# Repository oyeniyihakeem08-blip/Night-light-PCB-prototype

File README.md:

# Wireless Smart Night Light System

A smart, motion-sensing LED night light that runs straight from the mains, keeps working through power cuts on its own battery, and is controlled by a paired wireless remote.

I designed and built both custom PCBs end to end: schematic, PCB layout, power design, component selection and firmware for **both** the light and the remote.

## Highlights

- **Mains to light, all on one board:** 100 to 240 VAC input, isolated 5 V conversion, battery charging, 3.3 V logic, RF, sensing and a six-LED lighting array.
- **Seamless battery backup:** an 18650 Li-ion cell takes over automatically during a power outage, designed for about 24 hours of operation.
- **Smart behaviour:** the light turns on only when it is dark **and** someone moves, then stays on while motion continues.
- **Secure pairing:** a remote pairs with the light using a random 32-bit token, then talks to it on a private radio address that only that light listens to.
- **Hardware-level battery protection:** a nanopower comparator with hysteresis shuts the 3.3 V rail down at low battery, without depending on firmware.
- **Battery-friendly remote:** the remote sleeps between button presses and wakes on demand, so a small battery goes a long way.

## Hardware

### Main unit (the night light)

| Block | Part | Role |
| --- | --- | --- |
| Mains conversion | HLK-5M05 | Isolated 100 to 240 VAC to 5 V module, 5 W |
| Charger and power path | BQ24074RGT | Charges the battery, powers the system from the supply, switches to battery during an outage |
| Battery | 18650 Li-ion, 3000 mAh | Backup energy storage |
| Low-battery switching | TLV3012 comparator + AO3400A + AO3407A | Hardware cutoff with hysteresis |
| 3.3 V regulator | TLV75533 | Clean rail for MCU, RF and PIR |
| Microcontroller | STM32G031K8T6 | State machine, RF, sensing, LED control |
| Wireless | nRF24L01+ | 2.4 GHz link to the remote |
| Motion sensing | BISS0001 + PIR element | Presence detection |
| Light sensing | GL5528 LDR | Day/night detection via the ADC |
| Lighting | 6x Samsung LM281B+ (SPMWH1228MD5WATUVK) | Illumination, driven through an AO3400A MOSFET |
| Programming | SWD Tag-Connect | Flash and debug the STM32 |

### Wireless remote

| Block | Part | Role |
| --- | --- | --- |
| Microcontroller | ATtiny1616 | Remote controller |
| Wireless | nRF24L01+ | 2.4 GHz link to the light |
| Inputs | 3 buttons | Power, Sensor On, Sensor Off |
| Power | 2x AAA | Direct 3 V operation, no regulator needed |

### Board views

| | Design | Fabricated |
|---|---|---|
| **Front** |  |  |
| **Back** |  |  |

### Schematic

## Engineering decisions

### Charger, power path and input limiting

The BQ24074 is set for a **500 mA** charge current (1.8 k ISET resistor) and a **600 mA input current limit** (2.7 k ILIM resistor). The input limit is deliberate: it keeps total draw within what the HLK-5M05 can supply and prevents the module from overheating inside a compact enclosure.

### Low-battery cutoff in hardware, with hysteresis

A TLV3012 nanopower comparator with a built-in reference watches the battery through a 174 k / 100 k divider. A 1 M feedback resistor adds **hysteresis**, so the circuit turns the system **off at about 3.4 V** and only turns it **back on at about 3.6 V**. The comparator drives an N-MOSFET (AO3400A) that controls a high-side P-MOSFET (AO3407A) feeding the 3.3 V regulator. The result is a clean shutdown with no oscillation, and no dependence on firmware to protect the battery.

### Low-noise LED drive

Dedicated constant-current ICs (such as NSI45020 and AL5809) were evaluated and rejected: they need voltage headroom that is not available as the battery falls from 4.2 V towards 3.4 V. Instead, the six LEDs each have a 33 ohm series resistor and are switched through a MOSFET. It works across the full battery range, adds no switching noise and keeps the part count low.

### A 3.3 V rail chosen for the radio

The TLV75533 was picked for its fast transient response, which handles the current spikes of the nRF24L01+, and for its low output noise, which keeps the PIR and RF stable.

### Isolation from the mains

Mains conversion is handled by a pre-built isolated AC-DC module, so everything downstream is low voltage. It also keeps the design simpler and lowers certification risk compared with a discrete flyback.

### Battery connector protection

A P-MOSFET (AO3407A) sits in series with the battery connector, which provides reverse-polarity protection.

### Light sensor is read only while the light is off

If the LDR were read while the LEDs are on, the light would be measuring its own output and the system would flip-flop between states. The firmware therefore reads the LDR only when the light is off, and waits for it to settle after the light switches off before sampling.

## Design evolution

I started this project with a written system architecture, and the final board differs from it in three places. I made each change deliberately during development.

| Area | Initial architecture | Final design | Why it changed |
| --- | --- | --- | --- |
| PIR front-end | NCS36000 | BISS0001 | The original chip could not be sourced, so I found a suitable replacement and redesigned the sensor circuit around it to keep the build moving without compromising the design. |
| Remote buttons | 2 buttons | 3 buttons (Power, Sensor On, Sensor Off) | Improved during development. Separate Sensor On and Sensor Off buttons make the remote clearer and more direct to use, while Power handles toggling, pairing and reset. |
| Pairing | Remote sends a unique ID, which the light stores | Random 32-bit token, stored with the remote's ID, then a private radio address | Chosen for security and for a better experience for users and engineers (see below). |

### Why pairing was redesigned

The first plan relied on a fixed unique ID from the remote. That works, but it leaves a reusable identifier that never changes, and it keeps all traffic on one shared address where neighbouring units can interfere with each other.

The final scheme is more robust:

- **A fresh secret for every pairing.** The light generates a 32-bit token each time a remote is paired, so there is no fixed identifier to copy or reuse. Every command afterwards must carry that token, and the light ignores anything that does not match.
- **A private address after pairing.** Once paired, commands travel on a private radio address that belongs to that remote and that only its light listens to. The shared public address is used only for pairing and factory reset, which keeps everyday traffic off it and reduces interference between nearby units.
- **A short, clear pairing window.** Pairing is only open for 60 seconds after power-up, with LED feedback at every step, so users and installers always know what state the light is in.
- **A safe way out.** A 6 second factory reset clears the stored pairing, so a lost or replaced remote never leaves the light locked to a remote nobody has.

## How it behaves

### Light modes

| Mode | What the light does |
| --- | --- |
| Smart Idle | Light is off. The LDR is read to check if the room is dark. If it is dark and the PIR sees motion, the light turns on and moves to Smart Active. If the room is bright, motion is ignored. |
| Smart Active | Light is on. The LDR is no longer read, so room lights or sunrise do not switch it off. Every movement restarts a 60 second countdown, and when 60 seconds pass with no motion the light turns off and returns to Smart Idle. |
| Forced On | Power pressed while sensors are enabled. The light turns on and stays on. Motion and the LDR are ignored and the 60 second timer is paused. |
| Manual Mode | Sensor Off pressed. Both sensors are disabled and the light is a plain remote-controlled lamp: Power turns it on, Power again turns it off. |

### Remote buttons

| Button | Action |
| --- | --- |
| Power | Tap: toggle the light. Hold 3 seconds: start pairing. Hold 6 seconds: factory reset. |
| Sensor On | Tap: re-enable the motion and light sensors. |
| Sensor Off | Tap: disable the sensors and switch to manual mode. |

### Pairing, step by step

1. On first power-up the light enters pairing mode for up to 60 seconds. Its LED blinks slowly (1 second on, 2 seconds off) while it listens on the public address.
2. On the remote I hold Power for 3 seconds. The remote sends a pairing request and blinks its LED (1 second on, 2 seconds off) while it waits.
3. The light generates a random 32-bit token, stores it with the remote's address in permanent memory and replies with a confirmation.
4. The remote receives the confirmation, blinks twice quickly and switches to its private address. The light confirms with a long double blink (3 seconds on, 2 off, 3 on), and normal operation starts.
5. If nobody pairs within 60 seconds, the light stops blinking and runs in smart (sensor) mode. Until a remote is paired, it cannot be switched on or off or have its sensor mode changed.

To pair a new remote later, for example after losing the first, I hold Power for 6 seconds. This sends a factory reset, which clears the stored pairing; the light blinks 6 times and goes back into pairing mode. Factory reset is the only command the light accepts on the public address after pairing.

### LED feedback

The light's LED only blinks to report:

- Slow blink (1 second on, 2 seconds off): pairing mode, waiting for a remote.
- Long double blink (3 seconds on, 2 off, 3 on): paired successfully.
- One short flash: sensors turned on.
- Two short flashes: sensors turned off.

The remote LED responds to every button press: one blink means the light received the command, three fast blinks mean it failed.

### Remote power saving

The remote does not run a loop. It sleeps fully between presses, drawing under a microamp, and wakes in microseconds when any button is pressed. It then sends its command, waits for the acknowledgement, blinks its LED and goes straight back to sleep, so two AAA cells go a long way.

## Firmware and radio link

Both units run PlatformIO projects using the Arduino framework with the RF24 library for the nRF24L01+. The firmware is layered so that hardware drivers, the radio, pairing and the application logic are kept in separate modules.

### Radio settings

| Setting | Value |
| --- | --- |
| Frequency channel | 76 (2.476 GHz) |
| Data rate | 250 kbps |
| Transmit power | PA_LOW |
| Auto-retry | up to 15 retries (delay setting 5) |
| Public address (pipe 0) | `E7:E7:E7:E7:E7`, used only for pairing and factory reset |
| Private address (pipe 1) | the remote's own unique 5-byte address, assigned at pairing |

250 kbps gives the best receiver sensitivity and range on the nRF24L01+, and low transmit power keeps current draw down on the remote's two AAA cells.

### Packet format

Every message is a fixed 11 byte packet:

```c
struct Packet {
    uint8_t  cmd;            // command code
    uint32_t token;          // pairing token
    uint8_t  remote_addr[5]; // remote's private address
    uint8_t  nonce;          // per-message value
};
```

| Command | Code | Sent on |
| --- | --- | --- |
| CMD_PAIR | 0x01 | public address |
| CMD_PAIR_ACK | 0x02 | public address |
| CMD_FACTORY_RESET | 0x03 | public address |
| CMD_POWER_ON | 0x10 | private address |
| CMD_POWER_OFF | 0x11 | private address |
| CMD_SENSOR_ON | 0x12 | private address |
| CMD_SENSOR_OFF | 0x13 | private address |

### How the light handles a packet

- On the public address (pipe 0), a paired light accepts only a factory reset.
- On the private address (pipe 1), the light checks the token first. A packet with a wrong token is dropped; a valid one goes to the light controller, which acts on the command.
- The pairing token is built from the lowest bit of 32 LDR ADC readings, mixed with the system timer, so it does not depend on a fixed seed. It is stored in EEPROM so pairing survives power cuts and battery loss.
- The bulb runs the independent watchdog (IWDG) so that a stuck firmware loop resets itself.

## Manufacturing

BOM, Gerber and pick-and-place files for JLCPCB / LCSC.

## Repository layout

```text
.
├── README.md
├── Night light PCB.kicad_pro      # KiCad project
├── Night light PCB.kicad_sch      # schematic
├── Night light PCB.kicad_pcb      # PCB layout
├── fp-lib-table                   # footprint library paths
├── sym-lib-table                  # symbol library paths
├── Footprint/                     # custom footprint libraries
├── Symbol/                        # custom symbol libraries
├── 3D Model/                      # 3D models used by the footprints
├── Night light PCB (Kicad and production files)/
│   └── Design filess/
│       ├── Night light PCB 3D model/
│       │   ├── Night Light board.step
│       │   ├── Night Light remote board.step
│       │   └── Night light PCB.step
│       ├── production/            # JLCPCB manufacturing outputs
│       │   ├── backups/
│       │   ├── bom.csv
│       │   ├── designators.csv
│       │   ├── netlist.ipc
│       │   ├── Night_light_PCB.zip
│       │   └── positions.csv
│       ├── Night light PCB BOM .csv
│       ├── Night light PCB-F_Fab.svg
│       ├── Night light PCB-NPTH-drl_map.pdf
│       ├── Night light PCB-PTH-drl_map.pdf
│       └── Night light Schematics.pdf
├── Firmware source file/          # firmware source projects
├── firmwares/                     # firmware builds
├── Documents/                     # project documents
└── Images/                        # photos, layouts and schematic used in this README
```

## Author

Hakeem Oyebisi · [oyebisihakeem@gmail.com](mailto:oyebisihakeem@gmail.com) · [GitHub](https://github.com/oyeniyihakeem08-blip)

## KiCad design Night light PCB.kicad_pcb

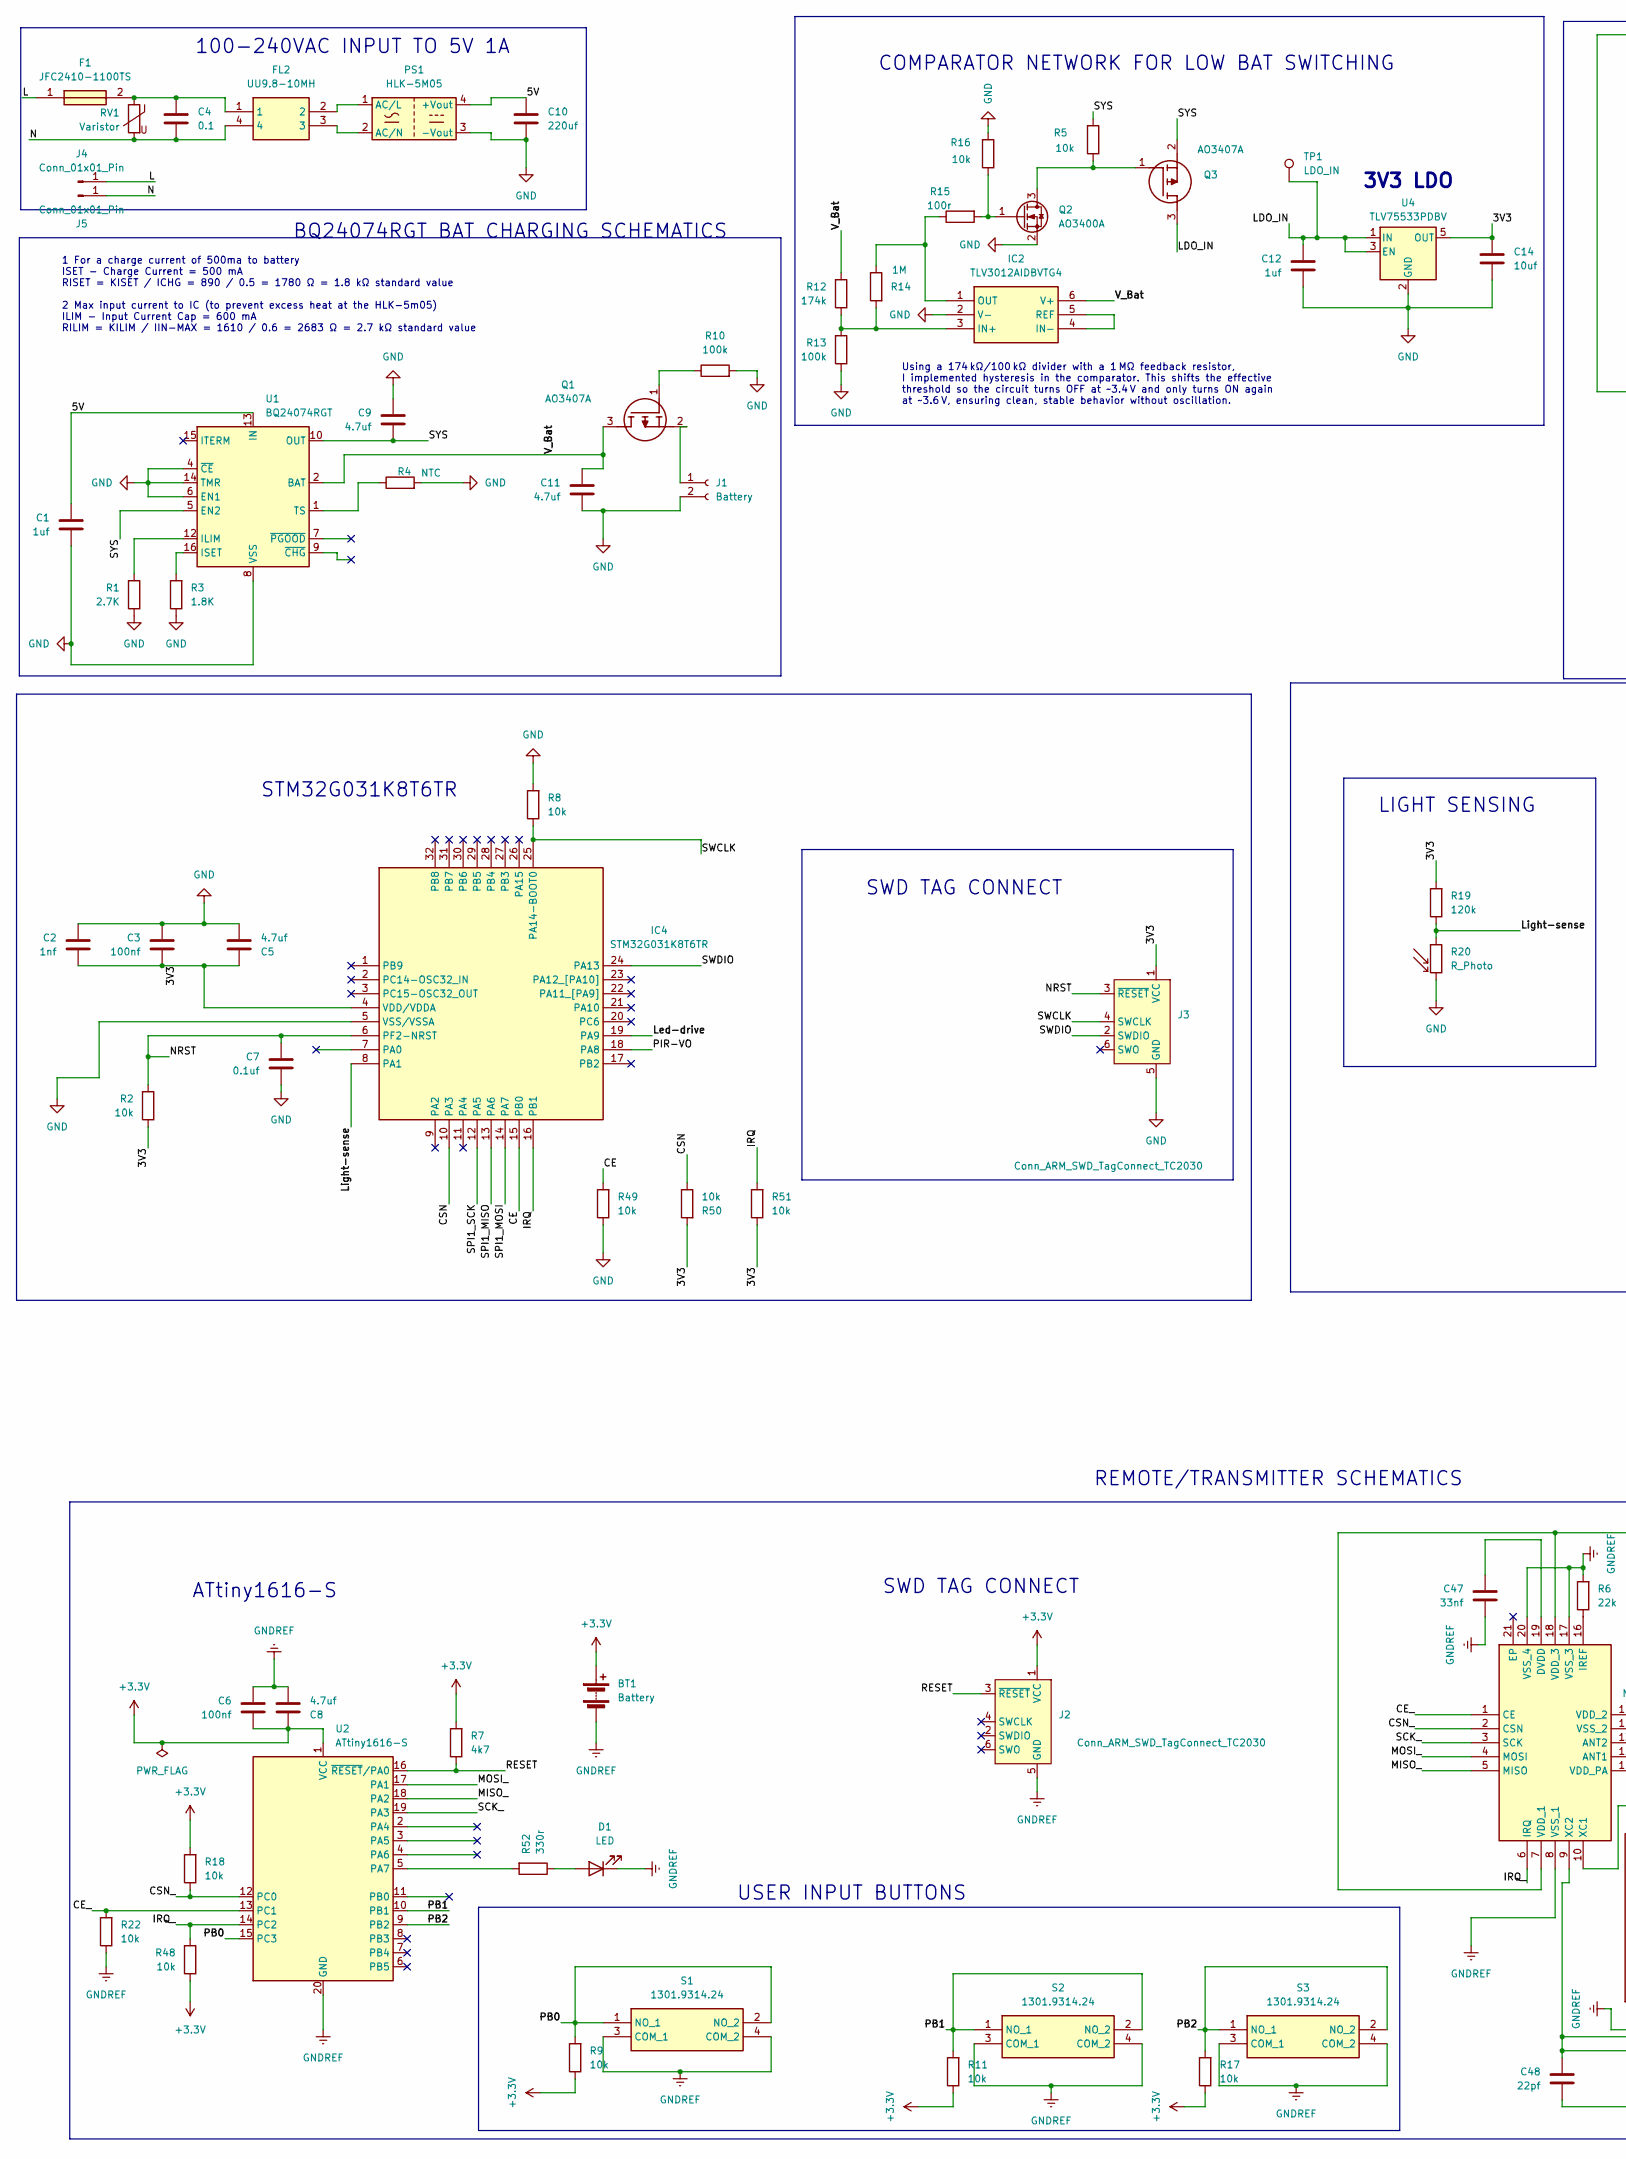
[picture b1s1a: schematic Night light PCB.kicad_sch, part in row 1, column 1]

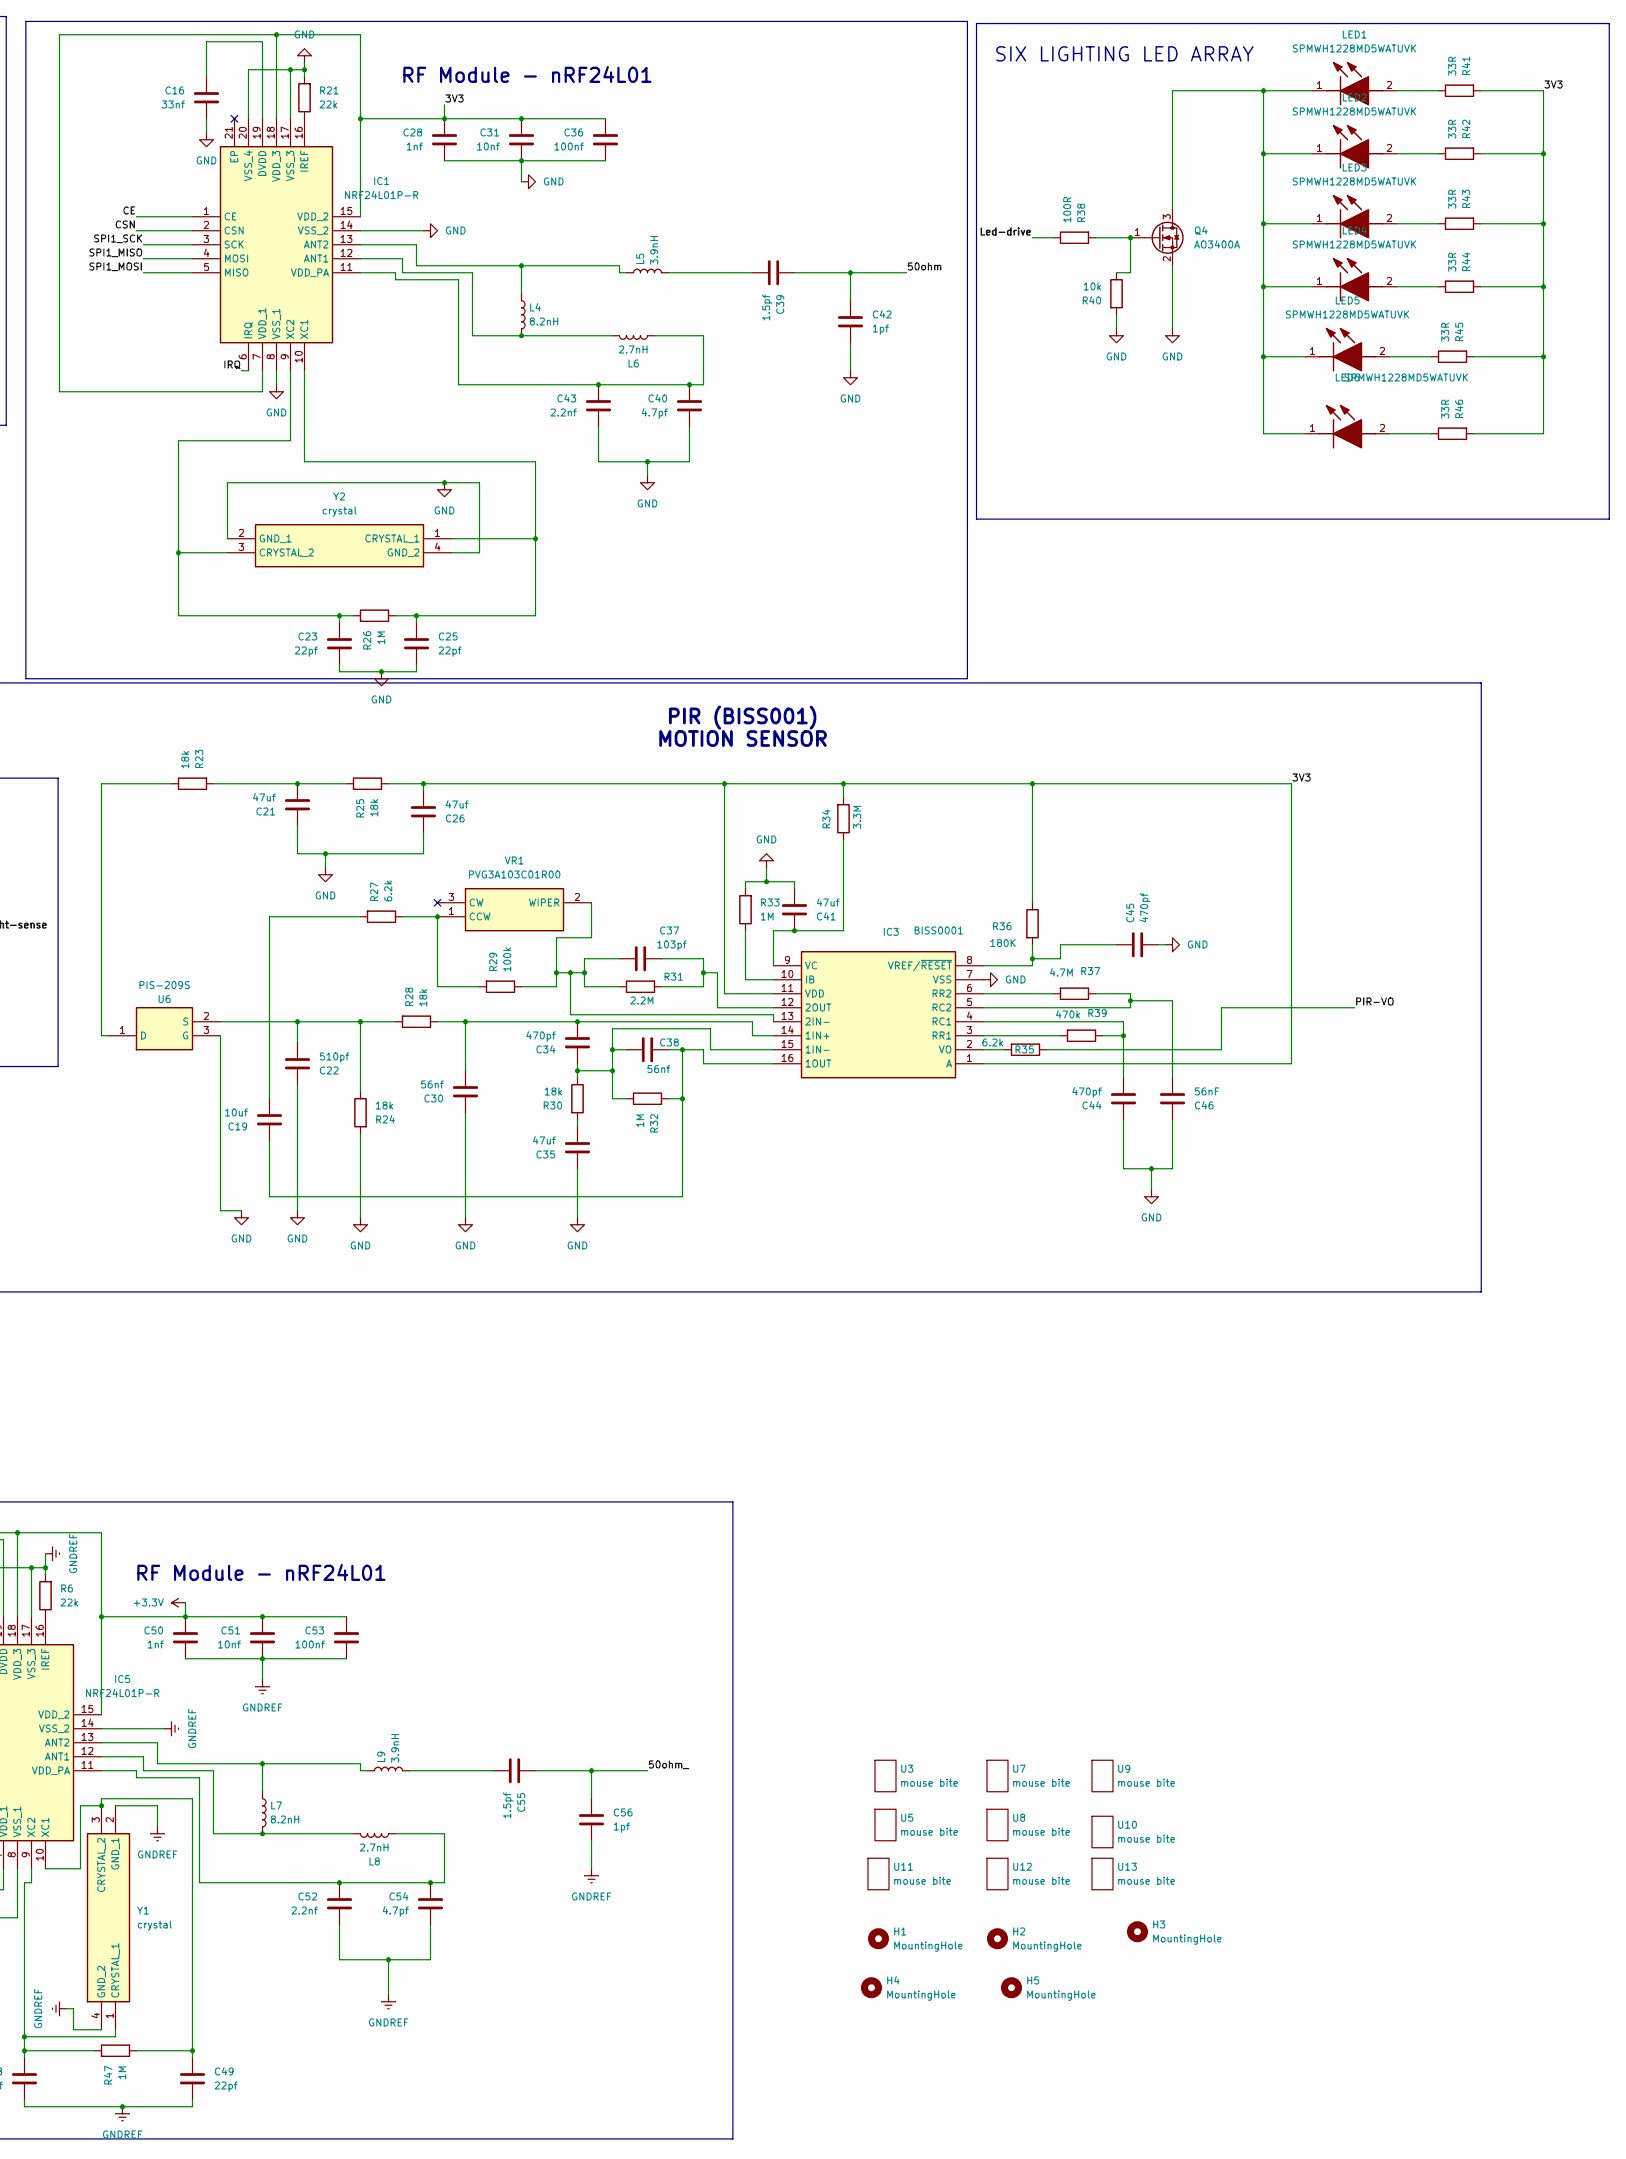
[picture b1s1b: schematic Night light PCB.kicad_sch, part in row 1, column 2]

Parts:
BT1: Battery; BatteryHolder_Keystone_2468_2xAAA; LCSC Part # BC2AAAPC
C1: 1uf; C_0402_1005Metric; LCSC Part # C29266
C2: 1nf; C_0805_2012Metric; LCSC Part # C94121
C3, C6: 100nf; C_0805_2012Metric; LCSC Part # C49678
C4: 0.1; C_Rect_L13.0mm_W8.0mm_P10.00mm_FKS3_FKP3_MKS4; LCSC Part # C46638858
C5, C8, C9, C11: 4.7uf; C_0805_2012Metric; LCSC Part # C98192
C7: 0.1uf; C_0805_2012Metric; LCSC Part # C49678
C10: 220uf; C_Elec_6.3x7.7; LCSC Part # C2887273
C12: 1uf; C_0805_2012Metric; LCSC Part # C28323
C14: 10uf; C_0805_2012Metric; LCSC Part # C95841
C16, C47: 33nf; C_0402_1005Metric; LCSC Part # C106862
C19: 10uf; C_1210_3225Metric; LCSC Part # C2918502
C21, C26, C35, C41: 47uf; C_1210_3225Metric; LCSC Part # C5440143
C22: 510pf; C_0402_1005Metric; LCSC Part # C18185763
C23, C25, C48, C49: 22pf; C_0402_1005Metric; LCSC Part # C277482
C28, C50: 1nf; C_0402_1005Metric; LCSC Part # C76947
C30, C38: 56nf; C_0402_1005Metric; LCSC Part # C36911349
C31, C51: 10nf; C_0402_1005Metric; LCSC Part # C15195
C34, C44, C45: 470pf; C_0402_1005Metric; LCSC Part # C701296
C36, C53: 100nf; C_0402_1005Metric; LCSC Part # C60474
C37: 103pf; C_0402_1005Metric; LCSC Part # C327009
C39, C55: 1.5pf; C_0402_1005Metric; LCSC Part # C1552
C40, C54: 4.7pf; C_0402_1005Metric; LCSC Part # C1569
C42, C56: 1pf; C_0402_1005Metric; LCSC Part # C710646
C43, C52: 2.2nf; C_0402_1005Metric; LCSC Part # C2987940
C46: 56nF; C_0402_1005Metric; LCSC Part # C36911349
D1: LED; LED_0402_1005Metric; LCSC Part # C21260817
F1: JFC2410-1100TS; FUSC10131X330N; Manufacturer_Part_Number SF-3812TL100T-2; Mouser Part Number 652-SF-3812TL100T-2
FL2: UU9.8-10MH; UU9810MH; Manufacturer_Part_Number UU9.8-10MH; LCSC Part # C148474
H1, H2, H3, H4, H5: MountingHole; MountingHole_3.2mm_M3
IC1, IC5: NRF24L01P-R; QFN50P400X400X95-21N-D; Manufacturer_Part_Number NRF24L01P-R; Mouser Part Number 949-NRF24L01P-R
IC2: TLV3012AIDBVTG4; SOT95P280X145-6N; Manufacturer_Part_Number TLV3012AIDBVTG4; Mouser Part Number 595-TLV3012AIDBVTG4
IC3: BISS0001; SOIC127P600X160-16N; Manufacturer_Part_Number BISS0001; LCSC Part # C18164474
IC4: STM32G031K8T6TR; QFP80P900X900X160-32N; Manufacturer_Part_Number STM32G031K8T6TR; Mouser Part Number 511-STM32G031K8T6TR
J1: Battery; JST_EH_B2B-EH-A_1x02_P2.50mm_Vertical; LCSC Part # C160262
J2, J3: Conn_ARM_SWD_TagConnect_TC2030; Tag-Connect_TC2030-IDC-FP_2x03_P1.27mm_Vertical
J4, J5: Conn_01x01_Pin; TestPoint_Keystone_5010-5014_Multipurpose
L4, L7: 8.2nH; L_0402_1005Metric; LCSC Part # C84404
L5, L9: 3.9nH; L_0402_1005Metric; LCSC Part # C5452416
L6, L8: 2.7nH; L_0402_1005Metric; LCSC Part # C77108
LED1, LED2, LED3, LED4, LED5, LED6: SPMWH1228MD5WATUVK; Manufacturer_Part_Number SPMWH1228MD5WATUVK; LCSC Part # 1510-SPMWH1228MD7WATUVKTR-ND
PS1: HLK-5M05; Converter_ACDC_Hi-Link_HLK-5Mxx; LCSC Part # C209907
Q1, Q3: AO3407A; SOT95P280X125-3N; Manufacturer_Part_Number AO3407A; LCSC Part # C15155
Q2, Q4: AO3400A; SOT-23; LCSC Part # C20917
R1: 2.7K; R_0402_1005Metric; LCSC Part # C138017
R2, R5, R8, R9, R11, R16, R17, R18, R22, R40, R48, R49, R50, R51: 10k; R_0402_1005Metric; LCSC Part # C60490
R3: 1.8K; R_0402_1005Metric; LCSC Part # C163481
R4: NTC; R_0402_1005Metric
R6, R21: 22k; R_0402_1005Metric; LCSC Part # C82868
R7: 4k7; R_0402_1005Metric; LCSC Part # C105871
R10, R13, R29: 100k; R_0402_1005Metric; LCSC Part # C60491
R12: 174k; R_0402_1005Metric; LCSC Part # C4214842
R14, R26, R32, R33, R47: 1M; R_0402_1005Metric; LCSC Part # C138033
R15: 100r; R_0402_1005Metric; LCSC Part # C106232
R19: 120k; R_0402_1005Metric; LCSC Part # C60490
R20: R_Photo; R_LDR_5.0x4.1mm_P3mm_Vertical; LCSC Part # C125627
R23, R24, R25, R28, R30: 18k; R_0402_1005Metric; LCSC Part # C138044
R27, R35: 6.2k; R_0402_1005Metric; LCSC Part # C137946
R31: 2.2M; R_0402_1005Metric; LCSC Part # C203143
R34: 3.3M; R_0402_1005Metric; LCSC Part # C482174
R36: 180K; R_0402_1005Metric; LCSC Part # C25760
R37: 4.7M; R_0402_1005Metric; LCSC Part # C3013173
R38: 100R; R_0402_1005Metric; LCSC Part # C106232
R39: 470k; R_0402_1005Metric; LCSC Part # C137976
R41, R42, R43, R44, R45, R46: 33R; R_0805_2012Metric; LCSC Part # C2907220
R52: 330r; R_0402_1005Metric; LCSC Part # C2097621
RV1: Varistor; RV_Disc_D12mm_W4.5mm_P7.5mm; LCSC Part # C2839517
S1, S2, S3: 1301.9314.24; 1301931424; Manufacturer_Part_Number 1301.9314.24; Mouser Part Number 693-1301.9314.24
TP1: LDO_IN; TestPoint_Pad_D4.0mm
U1: BQ24074RGT; VQFN-16-1EP_3x3mm_P0.5mm_EP1.6x1.6mm; LCSC Part # C54313
U2: ATtiny1616-S; SOIC-20W_7.5x12.8mm_P1.27mm; LCSC Part # C614136
U3, U5, U7, U8, U9, U10, U11, U12, U13: mouse bite; mouse-bite-2mm-4mm
U4: TLV75533PDBV; SOT-23-5; LCSC Part # C404027
U6: PIS-209S; PIS209S; Manufacturer_Part_Number PIS-209S
VR1: PVG3A103C01R00; Manufacturer_Part_Number PVG3A103C01R00; Mouser Part Number 81-PVG3A103C01R00
Y1, Y2: crystal; X322516MOB4SI; Manufacturer_Part_Number X322516MOB4SI; LCSC Part # C12668

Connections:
+3.3V: BT1.1 (+), C6.2, C8.1, C50.1, C51.1, C53.1, IC5.7 (VDD_1), IC5.15 (VDD_2), IC5.18 (VDD_3), J2.1 (VCC), R7.2, R9.1, R11.1, R17.1, R18.2, R48.1, U2.1 (VCC)
/3V3: C2.2, C3.2, C5.1, C14.1, C26.2, C28.1, C31.1, C36.1, IC1.7 (VDD_1), IC1.15 (VDD_2), IC1.18 (VDD_3), IC3.1 (A), IC3.11 (VDD), IC4.4 (VDD/VDDA), J3.1 (VCC), R2.1, R19.2, R25.1, R34.2, R36.1, R41.2, R42.2, R43.2, R44.2, R45.2, R46.2, R50.2, R51.1, U4.5 (OUT)
/5V: C1.1, C10.1, PS1.4 (+Vout), U1.13 (IN)
/50ohm: C39.1, C42.1
/50ohm_: C55.1, C56.1
/CE: IC1.1 (CE), IC4.15 (PB0), R49.2
/CE_: IC5.1 (CE), R22.2, U2.13 (PC1)
/CSN: IC1.2 (CSN), IC4.10 (PA3), R50.1
/CSN_: IC5.2 (CSN), R18.1, U2.12 (PC0)
/IRQ: IC1.6 (IRQ), IC4.16 (PB1), R51.2
/IRQ_: IC5.6 (IRQ), R48.2, U2.14 (PC2)
/L: F1.1, J4.1
/LDO_IN: C12.1, Q3.3 (D), TP1.1, U4.1 (IN), U4.3 (EN)
/Led-drive: IC4.19 (PA9), R38.1
/Light-sense: IC4.8 (PA1), R19.1, R20.1
/MISO_: IC5.5 (MISO), U2.18 (PA2)
/MOSI_: IC5.4 (MOSI), U2.17 (PA1)
/N: C4.2, FL2.4, J5.1, RV1.2
/NRST: C7.1, IC4.6 (PF2-NRST), J3.3 (~RESET), R2.2
/PB0: R9.2, S1.1 (NO_1), S1.2 (NO_2), U2.15 (PC3)
/PB1: R11.2, S2.1 (NO_1), S2.2 (NO_2), U2.10 (PB1)
/PB2: R17.2, S3.1 (NO_1), S3.2 (NO_2), U2.9 (PB2)
/PIR-VO: IC4.18 (PA8), R35.1
/RESET: J2.3 (~RESET), R7.1, U2.16 (~RESET/PA0)
/SCK_: IC5.3 (SCK), U2.19 (PA3)
/SPI1_MISO: IC1.4 (MOSI), IC4.13 (PA6)
/SPI1_MOSI: IC1.5 (MISO), IC4.14 (PA7)
/SPI1_SCK: IC1.3 (SCK), IC4.12 (PA5)
/SWCLK: IC4.25 (PA14-BOOT0), J3.4 (SWCLK), R8.1
/SWDIO: IC4.24 (PA13), J3.2 (SWDIO)
/SYS: C9.2, Q3.2 (S), R5.2, U1.5 (EN2), U1.10 (OUT), U1.11 (OUT)
/V_Bat: C11.1, IC2.6 (V+), Q1.3 (D), R12.2, U1.2 (BAT), U1.3 (BAT)
GND: C1.2, C2.1, C3.1, C5.2, C7.2, C9.1, C10.2, C11.2, C12.2, C14.2, C16.2, C21.1, C22.1, C23.2, C25.2, C26.1, C28.2, C30.1, C31.2, C35.1, C36.2, C40.2, C41.2, C42.2, C43.2, C44.1, C45.2, C46.1, IC1.8 (VSS_1), IC1.14 (VSS_2), IC1.17 (VSS_3), IC1.20 (VSS_4), IC2.2 (V-), IC3.7 (VSS), IC4.5 (VSS/VSSA), J1.2, J3.5 (GND), PS1.3 (-Vout), Q2.2 (S), Q4.2 (S), R1.1, R3.1, R4.2, R8.2, R10.2, R13.1, R16.2, R20.2, R21.2, R24.2, R33.2, R40.2, R49.1, U1.4 (~CE), U1.6 (EN1), U1.8 (VSS), U1.14 (TMR), U1.17 (VSS), U4.2 (GND), U6.3 (G), Y2.2 (GND_1), Y2.4 (GND_2)
GNDREF: BT1.2 (-), C6.1, C8.2, C47.2, C48.2, C49.2, C50.2, C51.2, C52.2, C53.2, C54.2, C56.2, D1.1 (K), IC5.8 (VSS_1), IC5.14 (VSS_2), IC5.17 (VSS_3), IC5.20 (VSS_4), J2.5 (GND), R6.2, R22.1, S1.3 (COM_1), S1.4 (COM_2), S2.3 (COM_1), S2.4 (COM_2), S3.3 (COM_1), S3.4 (COM_2), U2.20 (GND), Y1.2 (GND_1), Y1.4 (GND_2)
unnamed: C4.1, F1.2, FL2.1, RV1.1
unnamed: C19.2, R27.2
unnamed: C21.2, R23.2, R25.2
unnamed: C35.2, R30.2
unnamed: C39.2, L5.2
unnamed: C55.2, L9.2
unnamed: D1.2 (A), R52.1
unnamed: IC1.12 (ANT1), L4.2, L6.1
unnamed: IC1.13 (ANT2), L4.1, L5.1
unnamed: C16.1, IC1.19 (DVDD)
unnamed: IC1.16 (IREF), R21.1
unnamed: C40.1, C43.1, IC1.11 (VDD_PA), L6.2
unnamed: C25.1, IC1.10 (XC1), R26.1, Y2.1 (CRYSTAL_1)
unnamed: C23.1, IC1.9 (XC2), R26.2, Y2.3 (CRYSTAL_2)
unnamed: IC2.3 (IN+), R12.1, R13.2, R14.2
unnamed: IC2.4 (IN-), IC2.5 (REF)
unnamed: IC2.1 (OUT), R14.1, R15.1
unnamed: C30.2, C34.2, IC3.14 (1IN+), R28.1
unnamed: C34.1, C38.2, IC3.15 (1IN-), R30.1, R32.1
unnamed: C19.1, C38.1, IC3.16 (1OUT), R32.2
unnamed: C37.2, IC3.13 (2IN-), R29.1, R31.1, VR1.2 (WIPER)
unnamed: C37.1, IC3.12 (2OUT), R31.2
unnamed: IC3.10 (IB), R33.1
unnamed: C44.2, IC3.4 (RC1), R39.1
unnamed: C46.2, IC3.5 (RC2), R37.1
unnamed: IC3.3 (RR1), R39.2
unnamed: IC3.6 (RR2), R37.2
unnamed: C41.1, IC3.9 (VC), R34.1
unnamed: IC3.2 (VO), R35.2
unnamed: C45.1, IC3.8 (VREF/~RESET), R36.2
unnamed: IC5.12 (ANT1), L7.2, L8.1
unnamed: IC5.13 (ANT2), L7.1, L9.1
unnamed: C47.1, IC5.19 (DVDD)
unnamed: IC5.16 (IREF), R6.1
unnamed: C52.1, C54.1, IC5.11 (VDD_PA), L8.2
unnamed: C49.1, IC5.10 (XC1), R47.1, Y1.3 (CRYSTAL_2)
unnamed: C48.1, IC5.9 (XC2), R47.2, Y1.1 (CRYSTAL_1)
unnamed: J1.1, Q1.2 (S)
unnamed: LED1.2 (A), R41.1
unnamed: LED1.1 (K), LED2.1 (K), LED3.1 (K), LED4.1 (K), LED5.1 (K), LED6.1 (K), Q4.3 (D)
unnamed: LED2.2 (A), R42.1
unnamed: LED3.2 (A), R43.1
unnamed: LED4.2 (A), R44.1
unnamed: LED5.2 (A), R45.1
unnamed: LED6.2 (A), R46.1
unnamed: FL2.2, PS1.1 (AC/L)
unnamed: FL2.3, PS1.2 (AC/N)
unnamed: Q1.1 (G), R10.1
unnamed: Q2.3 (D), Q3.1 (G), R5.1
unnamed: Q2.1 (G), R15.2, R16.1
unnamed: Q4.1 (G), R38.2, R40.1
unnamed: R1.2, U1.12 (ILIM)
unnamed: R3.2, U1.16 (ISET)
unnamed: R4.1, U1.1 (TS)
unnamed: R52.2, U2.5 (PA7)
unnamed: R23.1, U6.1 (D)
unnamed: C22.2, R24.1, R28.2, U6.2 (S)
unnamed: R27.1, R29.2, VR1.1 (CCW)

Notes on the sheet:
REMOTE/TRANSMITTER SCHEMATICS
PIR (BISS001) MOTION SENSOR
3V3 LDO
SWD TAG CONNECT
BQ24074RGT BAT CHARGING SCHEMATICS
STM32G031K8T6TR
RF Module - nRF24L01
USER INPUT BUTTONS
1 For a charge current of 500ma to battery ISET - Charge Current = 500 mA RISET = KISET / ICHG = 890 / 0.5 = 1780 Ω = 1.8 kΩ standard value 2 Max input current to IC (to prevent excess heat at the HLK-5m05) ILIM - Input Current Cap = 600 mA RILIM = KILIM / IIN-MAX = 1610 / 0.6 = 2683 Ω = 2.7 kΩ sta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
COMPARATOR NETWORK FOR LOW BAT SWITCHING
SIX LIGHTING LED ARRAY
LIGHT SENSING
ATtiny1616-S
Using a 174 kΩ/100 kΩ divider with a 1 MΩ feedback resistor, I implemented hysteresis in the comparator. This shifts the effective threshold so the circuit turns OFF at ~3.4 V and only turns ON again at ~3.6 V, ensuring clean, stable behavior without oscillation.
100-240VAC INPUT TO 5V 1A

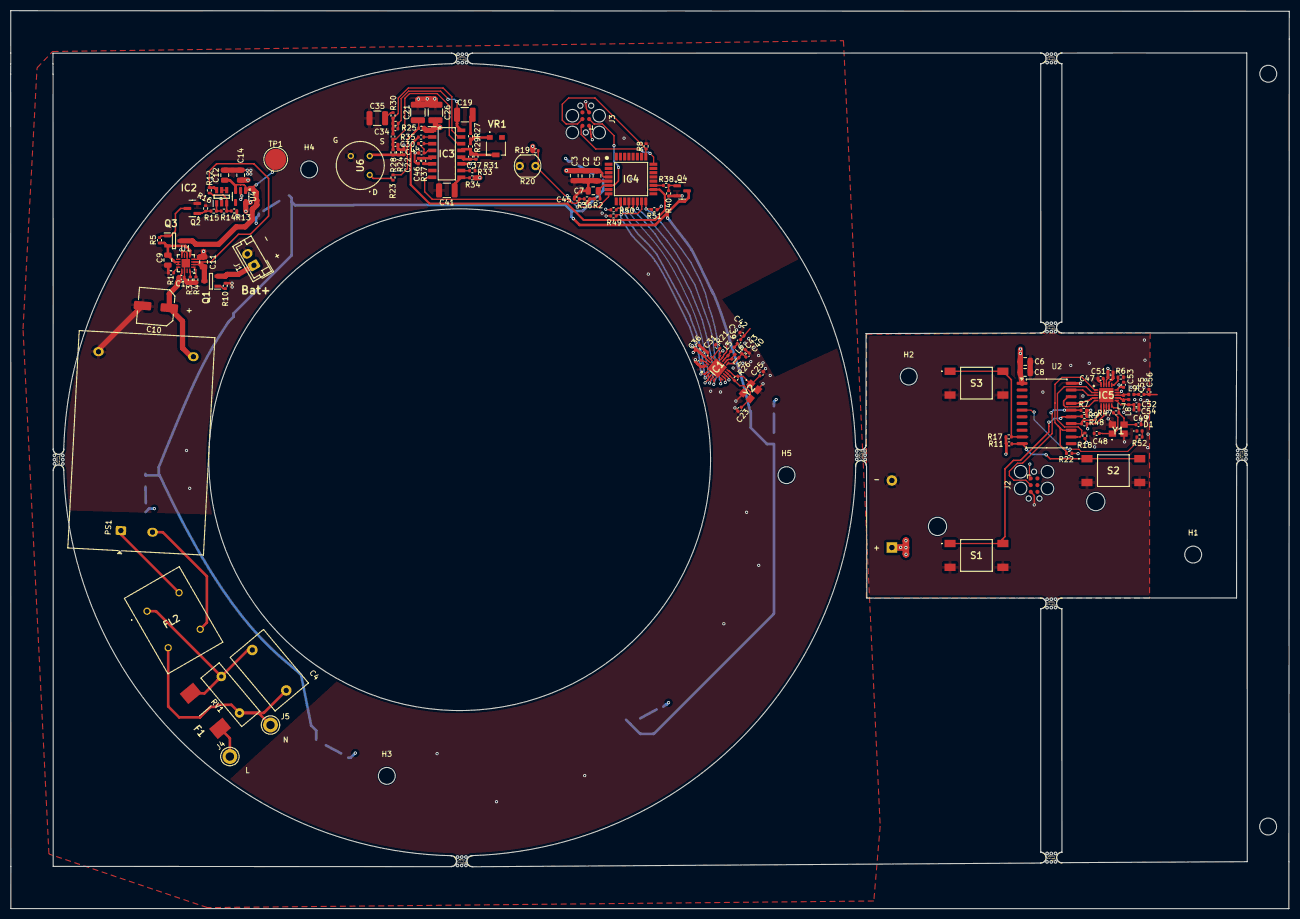
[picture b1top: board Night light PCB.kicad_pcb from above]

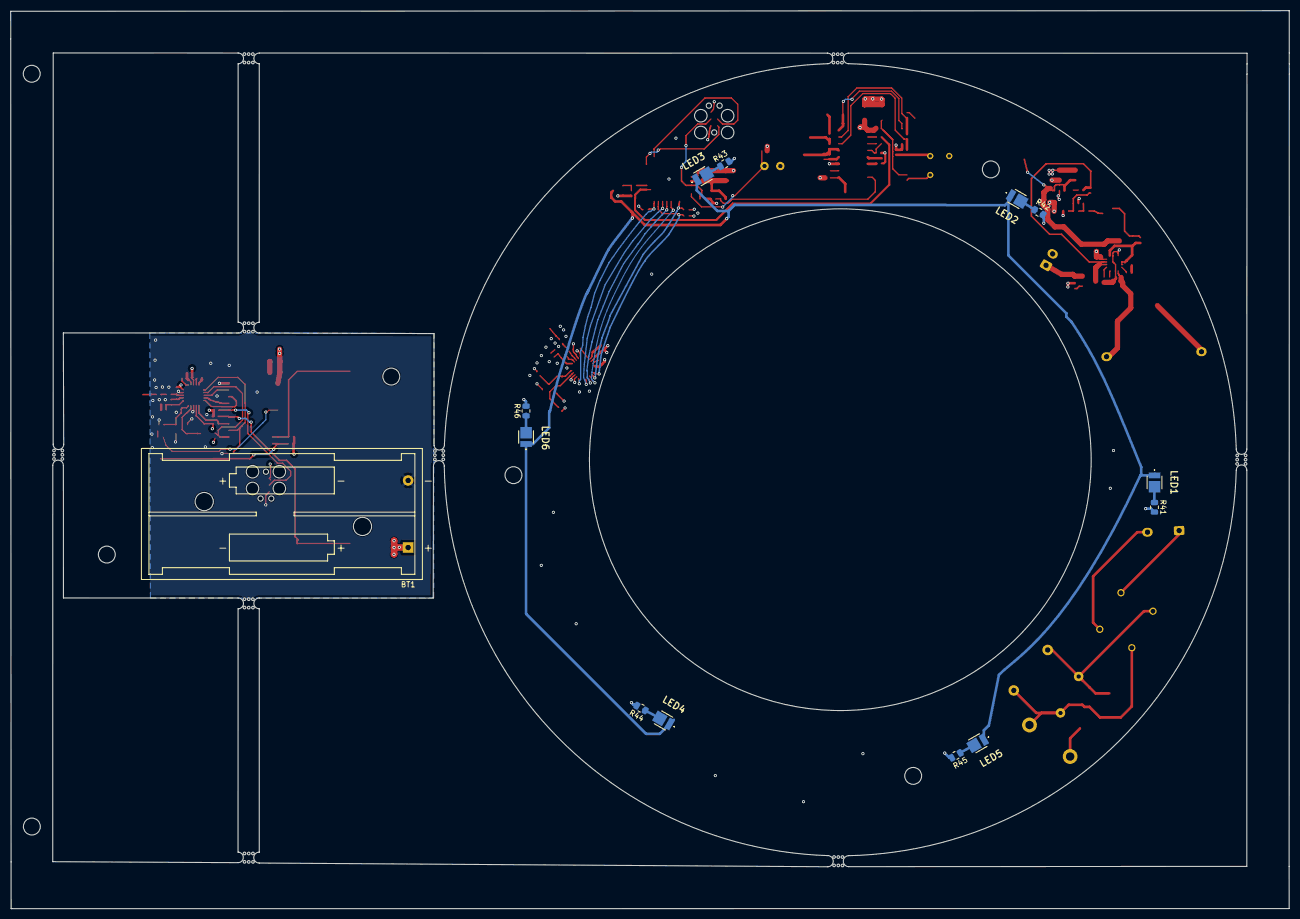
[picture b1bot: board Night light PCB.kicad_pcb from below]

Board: 4 copper layers, 242.1 x 170.0 mm, 155 parts (13 on the bottom side), 92 nets.

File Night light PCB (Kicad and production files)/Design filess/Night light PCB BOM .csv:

"Reference","Value","DNP","Exclude from BOM","Footprint","LCSC Part #"
"H1,H2,H3,H4,H5","MountingHole","","","MountingHole:MountingHole_3.2mm_M3",""
"J2,J3","Conn_ARM_SWD_TagConnect_TC2030","","","Connector:Tag-Connect_TC2030-IDC-FP_2x03_P1.27mm_Vertical",""
"J4,J5","Conn_01x01_Pin","","","TestPoint:TestPoint_Keystone_5010-5014_Multipurpose",""
"R4","NTC","","","Resistor_SMD:R_0402_1005Metric",""
"TP1","LDO_IN","","","TestPoint:TestPoint_Pad_D4.0mm",""
"U3,U5,U7,U8,U9,U10,U11,U12,U13","mouse bite","","","mouse bite:mouse-bite-2mm-4mm",""
"LED1,LED2,LED3,LED4,LED5,LED6","SPMWH1228MD5WATUVK","","","LED:SPMWH1228MD5WATUVK","1510-SPMWH1228MD7WATUVKTR-ND"
"BT1","Battery","","","Battery:BatteryHolder_Keystone_2468_2xAAA","BC2AAAPC"
"C39,C55","1.5pf","","","Capacitor_SMD:C_0402_1005Metric","C1552"
"C40,C54","4.7pf","","","Capacitor_SMD:C_0402_1005Metric","C1569"
"IC1,IC5","NRF24L01P-R","","","nRF24L01P:QFN50P400X400X95-21N-D","C8791"
"Y1,Y2","crystal","","","crystal:X322516MOB4SI","C12668"
"Q1,Q3","AO3407A","","","PMOS A03407:SOT95P280X125-3N","C15155"
"C31,C51","10nf","","","Capacitor_SMD:C_0402_1005Metric","C15195"
"Q2,Q4","AO3400A","","","Package_TO_SOT_SMD:SOT-23","C20917"
"R36","180K","","","Resistor_SMD:R_0402_1005Metric","C25760"
"C12","1uf","","","Capacitor_SMD:C_0805_2012Metric","C28323"
"C1","1uf","","","Capacitor_SMD:C_0402_1005Metric","C29266"
"C3,C6","100nf","","","Capacitor_SMD:C_0805_2012Metric","C49678"
"C7","0.1uf","","","Capacitor_SMD:C_0805_2012Metric","C49678"
"U1","BQ24074RGT","","","Package_DFN_QFN:VQFN-16-1EP_3x3mm_P0.5mm_EP1.6x1.6mm","C54313"
"C36,C53","100nf","","","Capacitor_SMD:C_0402_1005Metric","C60474"
"R2,R5,R8,R9,R11,R16,R17,R18,R22,R40,R48,R49,R50,R51","10k","","","Resistor_SMD:R_0402_1005Metric","C60490"
"R19","120k","","","Resistor_SMD:R_0402_1005Metric","C60490"
"R10,R13,R29","100k","","","Resistor_SMD:R_0402_1005Metric","C60491"
"IC2","TLV3012AIDBVTG4","","","TLV3012:SOT95P280X145-6N","C62505"
"C28,C50","1nf","","","Capacitor_SMD:C_0402_1005Metric","C76947"
"L6,L8","2.7nH","","","Inductor_SMD:L_0402_1005Metric","C77108"
"R6,R21","22k","","","Resistor_SMD:R_0402_1005Metric","C82868"
"R52","330r","","","Resistor_SMD:R_0402_1005Metric","C84256"
"L4,L7","8.2nH","","","Inductor_SMD:L_0402_1005Metric","C84404"
"C2","1nf","","","Capacitor_SMD:C_0805_2012Metric","C94121"
"C14","10uf","","","Capacitor_SMD:C_0805_2012Metric","C95841"
"C5,C8,C9,C11","4.7uf","","","Capacitor_SMD:C_0805_2012Metric","C98192"
"R7","4k7","","","Resistor_SMD:R_0402_1005Metric","C105871"
"R15","100r","","","Resistor_SMD:R_0402_1005Metric","C106232"
"R38","100R","","","Resistor_SMD:R_0402_1005Metric","C106232"
"C16,C47","33nf","","","Capacitor_SMD:C_0402_1005Metric","C106862"
"R20","R_Photo","","","OptoDevice:R_LDR_5.0x4.1mm_P3mm_Vertical","C125627"
"C10","220uf","","","Capacitor_SMD:C_Elec_6.3x7.7","C125977"
"F1","JFC2410-1100TS","","","FUSE:FUSC10131X330N","C136380"
"R27,R35","6.2k","","","Resistor_SMD:R_0402_1005Metric","C137946"
"R39","470k","","","Resistor_SMD:R_0402_1005Metric","C137976"
"R41,R42,R43,R44,R45,R46","33R","","","Resistor_SMD:R_0805_2012Metric","C138002"
"R1","2.7K","","","Resistor_SMD:R_0402_1005Metric","C138017"
"R14,R26,R32,R33,R47","1M","","","Resistor_SMD:R_0402_1005Metric","C138033"
"R23,R24,R25,R28,R30","18k","","","Resistor_SMD:R_0402_1005Metric","C138044"
"FL2","UU9.8-10MH","","","10MH CHOKE:UU9810MH","C148474"
"J1","Battery","","","Connector_JST:JST_EH_B2B-EH-A_1x02_P2.50mm_Vertical","C160262"
"R3","1.8K","","","Resistor_SMD:R_0402_1005Metric","C163481"
"R31","2.2M","","","Resistor_SMD:R_0402_1005Metric","C203143"
"PS1","HLK-5M05","","","Converter_ACDC:Converter_ACDC_Hi-Link_HLK-5Mxx","C209907"
"C23,C25,C48,C49","22pf","","","Capacitor_SMD:C_0402_1005Metric","C277482"
"C37","103pf","","","Capacitor_SMD:C_0402_1005Metric","C327009"
"U4","TLV75533PDBV","","","Package_TO_SOT_SMD:SOT-23-5","C404027"
"R34","3.3M","","","Resistor_SMD:R_0402_1005Metric","C482174"
"U2","ATtiny1616-S","","","Package_SO:SOIC-20W_7.5x12.8mm_P1.27mm","C614136"
"C34,C44,C45","470pf","","","Capacitor_SMD:C_0402_1005Metric","C701296"
"C42,C56","1pf","","","Capacitor_SMD:C_0402_1005Metric","C710646"
"IC4","STM32G031K8T6TR","","","STM32:QFP80P900X900X160-32N","C724044"
"VR1","PVG3A103C01R00","","","10k trimmer:PVG3A103C01R00","C780220"
"RV1","Varistor","","","Varistor:RV_Disc_D12mm_W4.5mm_P7.5mm","C2839517"
"C19","10uf","","","Capacitor_SMD:C_1210_3225Metric","C2918502"
"C43,C52","2.2nf","","","Capacitor_SMD:C_0402_1005Metric","C2987940"
"R37","4.7M","","","Resistor_SMD:R_0402_1005Metric","C3013173"
"R12","174k","","","Resistor_SMD:R_0402_1005Metric","C4214842"
"S1,S2,S3","1301.9314.24","","","Switch:1301931424","C4364459"
"C21,C26,C35,C41","47uf","","","Capacitor_SMD:C_1210_3225Metric","C5440143"
"L5,L9","3.9nH","","","Inductor_SMD:L_0402_1005Metric","C5452416"
"IC3","BISS0001","","","BISS0001:SOIC127P600X160-16N","C18164474"
"C22","510pf","","","Capacitor_SMD:C_0402_1005Metric","C18185763"
"D1","LED","","","LED_SMD:LED_0402_1005Metric","  C21260817"
"C30,C38","56nf","","","Capacitor_SMD:C_0402_1005Metric","C36911349"
"C46","56nF","","","Capacitor_SMD:C_0402_1005Metric","C36911349"
"C4","0.1","","","Capacitor_THT:C_Rect_L13.0mm_W8.0mm_P10.00mm_FKS3_FKP3_MKS4","C46638858"
"U6","PIS-209S","","","PIS209S:PIS209S","https://www.jotrin.com/product/parts/PIS209S"
